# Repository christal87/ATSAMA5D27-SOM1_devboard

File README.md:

# ATSAMA5D27-SOM1_devboard

A custom SAMA5D27 development board I made a while ago for personal experimentation. It's exposing the parallel NAND flash interface to get some hands-on experience using that as a traditional embedded boot device.  

#### TODO:
- [x] PMIC power sequencing works, voltage regulation feedbacks valid, ripple low
- [x] board unique ID readable
- [x] serial console works
- [x] RTC backup supercap works
- [x] default SDMMC0 boots
- [x] USB host VBUS present
- [x] USB High Speed host works
- [x] NAND r/w test OK
- [ ] Configure NAND IOSET and boot config
- [ ] Implement NAND support in the at91bootstrap 2nd level bootloader and U-Boot
- [ ] Compile a kernel and make a rootfs that boots from NAND (buildroot/linux4sam custom board and kernel configs)
- [ ] test (Q)SPI interfaces
- [ ] use (Q)SPI to store the bootloader as NVM
- [ ] test other interfaces (JTAG, UARTs, USB device, ethernet, I^2C, SPI, PIOBU, HSIC)
- [ ] bonus: design and add an eMMC breakout board

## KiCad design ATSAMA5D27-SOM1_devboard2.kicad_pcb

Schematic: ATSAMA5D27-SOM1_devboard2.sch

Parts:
C1, C2, C3, C4, C6, C24, C32: 10uF/25V; C_0805_2012Metric_Pad1.15x1.40mm_HandSolder; Part CL21A106KAYNNNG
C5, C10, C11, C12: 4.7uF/10V; C_0805_2012Metric_Pad1.15x1.40mm_HandSolder; Part CL21A475KPFNNNG
C7: 1F/5.5V; C_Disc_D11.0mm_W5.0mm_P5.00mm
C8, C9, C13, C15, C16, C18, C19, C22, C23, C25, C26, C27, C28, C30, C31, C33, C34, C35, C36, C37, C38, C41, C42, C43: 100nF; C_0805_2012Metric_Pad1.15x1.40mm_HandSolder; Part C0805C104M5RACTU
C14, C17, C20, C21: 2.2uF/16V; C_0805_2012Metric_Pad1.15x1.40mm_HandSolder; Part CL21A225KOFNNNE
C29: 20pF; C_0805_2012Metric_Pad1.15x1.40mm_HandSolder; Part C0805C200J5HACTU
C39, C40: 560pF; C_0805_2012Metric_Pad1.15x1.40mm_HandSolder; Part C0805C561M5RACTU
D1: STPS1L60ZF; D_SOD-123; Part STPS1L60ZF
D2: BAT54C; SOT-23; Part BAT54C
FB1, FB2, FB3, FB4, FB5, FB6, FB7, FB8: 180R; L_0805_2012Metric_Pad1.15x1.40mm_HandSolder; Part BLM21SP181SH1D
IC1: MIC23451-AAAYFL-T5; MIC23451AAAYFLT5; Manufacturer_Part_Number MIC23451-AAAYFL-T5; Mouser Part Number 998-MIC23451-AAAYFL
IC2: TMUX1219DCKR; SOT65P210X110-6N; Manufacturer_Part_Number TMUX1219DCKR; Mouser Part Number 595-TMUX1219DCKR
IC3: ATSAMA5D27-SOM1; ATSAMA5D27SOM1; Manufacturer_Part_Number ATSAMA5D27-SOM1; Mouser Part Number 556-ATSAMA5D27-SOM1
IC4, IC6, IC9: IS25LP512M-JLLE; SON127P800X600X80-9N; Manufacturer_Part_Number IS25LP512M-JLLE; Mouser Part Number 870-IS25LP512M-JLLE
IC5: MT29F32G08CBADBWP-12IT:D; SOP50P2000X120-48N; Manufacturer_Part_Number MT29F32G08ABAAAWP-ITZ:A; Mouser Part Number 340-200226-TRAY
IC7: NL17SZ126DFT2G; SOT65P210X110-5N; Manufacturer_Part_Number NL17SZ126DFT2G; Mouser Part Number 863-NL17SZ126DFT2G
IC8: MIC2025-1YM; SOIC127P602X173-8N; Manufacturer_Part_Number MIC2025-1YM; Mouser Part Number 998-MIC2025-1YM
IC10: ATA6561-GBQW-N; SON65P300X300X90-9N-D; Manufacturer_Part_Number ATA6561-GBQW-N; Mouser Part Number 579-ATA6561-GBQW-N
J2, J3: 22-28-4080; PinHeader_1x08_P2.54mm_Vertical; Part 22-28-4080
J4: 22-28-4020; PinHeader_1x02_P2.54mm_Vertical; Part 22-28-4020
J5: 77313-101-10LF; PinHeader_2x05_P2.54mm_Vertical_SMD; Part 77313-101-10LF
J6: PJ-102AH; BarrelJack_CUI_PJ-102AH_Horizontal; Part PJ-102AH
J7, J8, J9, J10, J11: 22-28-4050; PinHeader_1x05_P2.54mm_Vertical; Part 22-28-4050
J13: 87520-0010BLF; 875200010BLF; Manufacturer_Part_Number 87520-0010BLF; Mouser Part Number 649-87520-0010BLF
J14: 5-2337992-4 (w/o PoE: KRJ45-109NL); 523379924; Manufacturer_Part_Number 5-2337992-4; Mouser Part Number 571-5-2337992-4
J15: 10103594-0001LF; USB_Micro-B_Amphenol_10103594-0001LF_Horizontal; Part 10103594-0001LF
J16: DM1AA-SF-PEJ_21_; DM1AA-SF-PEJ_21__1; Manufacturer_Part_Number DM1AA-SF-PEJ(21); Mouser Part Number 798-DM1AA-SF-PEJ21
J17: 77313-101-16LF; PinHeader_2x08_P2.54mm_Vertical; Part 77313-101-16LF
J18, J20: 77313-101-10LF; PinHeader_2x05_P2.54mm_Vertical; Part 77313-101-10LF
J19: 77313-101-14LF; PinHeader_2x07_P2.54mm_Vertical; Part 77313-101-14LF
J21, J22: 22-28-4030; PinHeader_1x03_P2.54mm_Vertical; Part 22-28-4030
JP1, JP4, JP5, JP6: SolderJumper3; SolderJumper-3_P2.0mm_Open_TrianglePad1.0x1.5mm_NumberLabels; Part 22-28-4030
JP2, JP3, JP7, JP8, JP9, JP10: SolderJumper2; SolderJumper-2_P1.3mm_Open_TrianglePad1.0x1.5mm; Part 22-28-4020
L1, L2, L3: 1uH/2.2A; L_1210_3225Metric_Pad1.42x2.65mm_HandSolder; Part BRL3225T1R0M
Q1, Q2: BSS138; SOT-23
R1, R4, R5, R14, R18, R22, R23, R24, R25, R26, R27, R39, R41, R44, R45, R46, R47, R51, R53, R54, R56: 10k; R_0805_2012Metric_Pad1.15x1.40mm_HandSolder; Part CRCW080510K0FKEAC
R2, R3, R9, R11, R13, R17, R37, R40, R48: 100k; R_0805_2012Metric_Pad1.15x1.40mm_HandSolder; Part CRCW0805100KJNEAC
R6, R7, R8, R10, R20, R21, R34, R35, R36, R38, R60, R61, R63, R64: 0R; R_0805_2012Metric_Pad1.15x1.40mm_HandSolder; Part CRCW08050000Z0EAC
R12, R15, R16, R19, R58, R59: 100R; R_0805_2012Metric_Pad1.15x1.40mm_HandSolder; Part CRCW0805100RFKEAC
R28: 301k; R_0805_2012Metric_Pad1.15x1.40mm_HandSolder; Part CRCW0805301KFKEA
R29: 158k; R_0805_2012Metric_Pad1.15x1.40mm_HandSolder; Part CRCW0805158KFKEA
R30, R32: 309k; R_0805_2012Metric_Pad1.15x1.40mm_HandSolder; Part CRCW0805309KFKEA
R31, R33: 71.5k; R_0805_2012Metric_Pad1.15x1.40mm_HandSolder; Part CRCW080571K5FKEA
R42: 10k (DNP); R_0805_2012Metric_Pad1.15x1.40mm_HandSolder; Part CRCW080510K0FKEAC
R43: 10k; R_0805_2012Metric_Pad1.15x1.40mm_HandSolder; part CRCW080510K0FKEAC
R49, R50: 470R; R_0805_2012Metric_Pad1.15x1.40mm_HandSolder; Part CRCW0805470RFKEAC
R52: 200k; R_0805_2012Metric_Pad1.15x1.40mm_HandSolder; Part CRCW0805200KJNEAC
R55: 22k; R_0805_2012Metric_Pad1.15x1.40mm_HandSolder; Part CRCW080522K0FKEAC
R57: 4k7; R_0805_2012Metric_Pad1.15x1.40mm_HandSolder; Part CRCW08054K70FKEAC
R62: 120R; R_0805_2012Metric_Pad1.15x1.40mm_HandSolder; Part CRCW0805120RFKEAC
RN1, RN2: 68k; R_Cat16-4; Part CAY16-683J4LF
RN3, RN4: 330R; R_Cat16-4; Part CAY16-331J4LF
SW1, SW2, SW3: PTS645SM43SMTR92LFS; SW_SPST_PTS645; Part PTS645SM43SMTR92LFS
U1: NCP1117-3.3_SOT223; SOT-223-3_TabPin2
U2: MCP2551-I-SN; SOIC-8_3.9x4.9mm_P1.27mm

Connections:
BB_PWR_GOOD: IC1.13 (PG3), IC3.28 (PD08/NANDRDY), R14.1
CAN0_RX: C36.1, IC10.4 (RXD), JP6.1 (A)
CAN0_TX: IC10.1 (TXD), JP5.1 (A)
CAN1_RX: IC3.114 (PC27/PCK1/CANRX1/A16), R55.1, R56.1
CAN1_TX: IC3.115 (PC26/CANTX1/A15), U2.1 (TXD)
CLK_AUDIO: IC3.61 (CLK_AUDIO)
COMPN: IC3.64 (COMPN), J19.4
COMPP: IC3.63 (COMPP), J19.2
CS_QSPI1: IC6.1 (CE#), IC7.4 (OUT_Y), R47.2
DISABLE_BOOT: IC3.126 (DIS_BOOT), IC7.1 (OE), JP7.2, R45.2
D_UART1_RXD: IC3.23 (PD02/URXD1/A25), J10.5
D_UART1_TXD: IC3.24 (PD03/UTXD1/FIQ/NWAIT), J10.4
ETH_LED0: IC3.36 (ETH_LED0), J14.P11
ETH_RX+: IC3.38 (ETH_RXP), J14.P3
ETH_RX-: IC3.37 (ETH_RXM), J14.P6
ETH_TX+: IC3.41 (ETH_TXP), J14.P1
ETH_TX-: IC3.40 (ETH_TXM), J14.P2
FLEXCOM0_IO0: IC3.167 (PB28/LCDDAT17/FLEXCOM0_IO0/TIOA5), J3.4
FLEXCOM0_IO1: IC3.144 (PB29/LCDDAT18/FLEXCOM0_IO1/TIOB5), J3.5
FLEXCOM0_IO2: IC3.165 (PB30/LCDDAT19/FLEXCOM0_IO2/TCLK5), J3.6
FLEXCOM0_IO3: IC3.143 (PB31/LCDDAT20/FLEXCOM0_IO3), J3.7
FLEXCOM0_IO4: IC3.145 (PC00/LCDDAT21/FLEXCOM0_IO4), J3.8
FLEXCOM3_IO0: IC3.14 (PC20/ISI_D11/FLEXCOM3_IO0/A9), J2.4
FLEXCOM3_IO1: IC3.6 (PC19/ISI_D10/FLEXCOM3_IO1/A8), J2.5
FLEXCOM3_IO2: IC3.172 (PC18/ISI_D9/FLEXCOM3_IO2/A7), J2.6
FLEXCOM3_IO3: IC3.7 (PC21/ISI_PCK/FLEXCOM3_IO3/A10), J2.7
FLEXCOM3_IO4: IC3.11 (PC22/ISI_VSYNC/FLEXCOM3_IO4/A11), J2.8
FLEXCOM4_IO0: IC3.117 (PC28/FLEXCOM4_IO0/PCK2/A17)
FLEXCOM4_IO1: IC3.118 (PC29/FLEXCOM4_IO1/A18)
FLEXCOM4_IO2: IC3.120 (PC30/FLEXCOM4_IO2/A19)
FLEXCOM4_IO3: IC3.116 (PC31/FLEXCOM4_IO3/URXD3/A20)
FLEXCOM4_IO4: IC3.121 (PD00/FLEXCOM4_IO4/UTXD3/A23)
GND: C1.2, C2.2, C3.2, C4.2, C5.2, C6.2, C7.2, C8.2, C9.2, C10.2, C11.2, C12.2, C13.2, C14.2, C15.1, C16.1, C17.1, C18.1, C19.1, C20.1, C21.1, C22.2, C23.2, C24.2, C25.2, C26.2, C27.2, C28.2, C29.2, C30.2, C31.2, C32.2, C33.2, C34.2, C35.2, C36.2, C37.1, C38.2, C39.2, C40.2, C41.2, C42.2, C43.1, FB5.1, FB6.1, FB8.1, IC1.1 (PGND_1), IC1.2 (PGND_2), IC1.10 (PGND_3), IC1.11 (AGND_1), IC1.24 (AGND_2), IC1.27 (EP1), IC1.28 (EP2), IC2.3 (GND), IC3.1 (GND_00), IC3.10 (GND_01), IC3.18 (GND_02), IC3.26 (GND_03), IC3.31 (GND_04), IC3.39 (GND_05), IC3.42 (GND_06), IC3.43 (GND_07), IC3.50 (GND_08), IC3.56 (GND_09), IC3.62 (GND_10), IC3.66 (GND_11), IC3.69 (GND_12), IC3.72 (GND_13), IC3.75 (GND_14), IC3.88 (GND_15), IC3.89 (GND_16), IC3.98 (GND_17), IC3.107 (GND_18), IC3.130 (GND_19), IC3.131 (GND_20), IC3.149 (GND_21), IC3.166 (GND_22), IC3.171 (GND_23), IC3.176 (GND_24), IC4.4 (GND), IC5.13 (VSS_1), IC5.36 (VSS_2), IC6.4 (GND), IC7.3 (GND), IC8.3 (GND), IC9.4 (GND), IC10.2 (GND), IC10.9 (EP), J2.1, J3.1, J5.3, J5.5, J5.9, J6.2, J7.1, J8.1, J9.1, J10.1, J11.1, J13.4, J14.P10, J15.5 (GND), J16.3, J16.12 (WRITE_PROTECTION_SWITCH_2), J17.14, J17.15, J17.16, J18.10, J19.8, J19.10, J19.12, J19.14, J20.10, J21.2, J22.2, JP7.1, JP8.2, Q1.2 (S), Q2.2 (S), R5.2, R27.2, R29.2, R31.2, R33.2, R42.1, R52.1, R54.2, R55.2, R57.2, R60.1, SW1.2, SW2.2, SW3.2, U1.1 (GND), U2.2 (VSS)
HSIC_DATA: IC3.74 (DATA), J4.2
HSIC_STROBE: IC3.73 (STROBE), J4.1
JTAG_TCK: IC3.53 (PD27/JTAG_TCK), J5.4, R13.1
JTAG_TDI: IC3.51 (PD28/JTAG_TDI), J5.8, R11.1
JTAG_TDO: IC3.52 (PD29/JTAG_TDO), J5.6
JTAG_TMS: IC3.54 (PD30/JTAG_TMS), J5.2, R9.1
NAND_ALE: IC3.119 (PB00/SPI0_MOSI/PWMH1), IC5.17 (ALE)
NAND_CE: IC3.93 (PA31/SPI0_MISO/PWML0/CLASSD_L3), IC5.9 (CE#), R37.1
NAND_CLE: IC3.122 (PB01/SPI0_SPCK/PWML1/CLASSD_R0), IC5.16 (CLE)
NAND_D0: IC3.106 (PA22/FLEXCOM1_IO2/SPI1_SPCK/SDMMC1_CK/Q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), IC5.29 (DQ0)
NAND_D1: IC3.102 (PA23/FLEXCOM1_IO1/SPI1_MOSI/QSPI0_CS), IC5.30 (DQ1)
NAND_D2: IC3.99 (PA24/FLEXCOM1_IO0/SPI1_MISO/QSPI0_IO0), IC5.31 (DQ2)
NAND_D3: IC3.97 (PA25/FLEXCOM1_IO3/SPI1_NPCS0/QSPI0_IO1), IC5.32 (DQ3)
NAND_D4: IC3.100 (PA26/FLEXCOM1_IO4/SPI1_NPCS1/QSPI0_IO2), IC5.41 (DQ4)
NAND_D5: IC3.90 (PA27/TIOA1/SPI0_NPCS2/SPI1_NPCS2/SDMMC1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), IC5.42 (DQ5)
NAND_D6: IC3.95 (PA28/TIOB1/SPI0_NPCS3/SPI1_NPCS3/SDMMC1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), IC5.43 (DQ6)
NAND_D7: IC3.96 (PA29/TCLK1/SPI0_NPCS1/SDMMC1_WP/CLASSD_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), IC5.44 (DQ7)
NAND_RDY: IC3.138 (PC08/LCDDEN/FIQ/PCK0/UTXD1), R35.2
NAND_RE: IC3.124 (PB02/PWMFI0/CLASSD_R1), R36.2
NAND_WE: IC3.94 (PA30/SPI0_NPCS0/PWMH0/SDMMC1_CD/CLASSD_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), R38.2
NRST: IC3.60 (NRST), R10.1, R15.2
unnamed: C1.1, C2.1, C4.1, IC1.5 (PVIN2), IC1.8 (PVIN3), IC1.25 (PVIN1), JP1.2 (C), R8.2, R12.2
unnamed: C5.1, IC1.3 (AVIN1), IC1.6 (AVIN2), IC1.9 (AVIN3), R12.1
unnamed: C7.1, D2.1, R19.1
unnamed: C8.1, D2.3, JP2.1
unnamed: C22.1, J14.P4
unnamed: C23.1, J14.P5
unnamed: C28.1, C32.1, FB7.2, J13.1
unnamed: C39.1, R58.2
unnamed: C40.1, R59.2
unnamed: C41.1, IC10.5 (VIO), R61.2
unnamed: C43.2, R63.2, R64.1
unnamed: D1.1 (K), R19.2
unnamed: FB2.2, JP3.2
unnamed: FB5.2, J13.MH1, J13.MH2
unnamed: FB6.2, J15.6 (Shield)
unnamed: FB7.1, IC8.6 (OUT_1), IC8.8 (OUT_2)
unnamed: FB8.2, J14.MH1, J14.MH2, J14.P8
unnamed: IC1.4 (SW2), L1.1
unnamed: IC1.7 (SW3), L3.1
unnamed: IC1.14 (FB3), R32.2, R33.1
unnamed: IC1.15 (EN3), R20.2, R22.2, R23.2
unnamed: IC1.16 (PG2), R20.1
unnamed: IC1.17 (FB2), R28.2, R29.1
unnamed: IC1.19 (EN2), R21.2, R24.2, R25.2
unnamed: IC1.20 (PG1), R21.1
unnamed: IC1.21 (EN1), R26.2
unnamed: IC1.23 (FB1), R30.2, R31.1
unnamed: IC1.26 (SW1), L2.1
unnamed: IC2.5 (D), R34.2
unnamed: IC3.141 (PC01/LCDDAT22/CANTX0/SPI1_SPCK/I2SCK0), JP5.2 (C)
unnamed: IC3.146 (PC02/LCDDAT23/CANRX0/SPI1_MOSI/I2SMCK0), JP6.2 (C)
unnamed: IC5.7 (R/B#), R35.1, R39.1
unnamed: IC5.8 (RE#), R36.1
unnamed: IC5.18 (WE#), R38.1
unnamed: IC5.19 (WP#), R40.1, R42.2
unnamed: IC5.25 (DNU/VSSQ_1), IC5.48 (DNU/VSSQ_2), JP8.1
unnamed: IC5.34 (DNU/VCCQ_1), IC5.39 (DNU/VCCQ_2), JP9.1
unnamed: IC10.6 (CANL), J22.1, R64.2
unnamed: IC10.7 (CANH), J22.3, R63.1
unnamed: IC10.8 (STBY), R60.2
unnamed: J5.7, R6.1
unnamed: J5.10, R10.2
unnamed: J14.P9, R49.2
unnamed: J14.P12, R50.2
unnamed: J19.1, RN3.8 (R1.2)
unnamed: J19.3, RN3.7 (R2.2)
unnamed: J19.5, RN3.6 (R3.2)
unnamed: J19.7, RN3.5 (R4.2)
unnamed: J19.9, RN4.8 (R1.2)
unnamed: J19.11, RN4.7 (R2.2)
unnamed: J19.13, RN4.6 (R3.2)
unnamed: J21.1, R58.1, R62.2, U2.6 (CANL)
unnamed: J21.3, R59.1, R62.1, U2.7 (CANH)
unnamed: Q1.1 (G), R1.1, R2.1
unnamed: Q1.3 (D), Q2.1 (G), R3.1, SW1.1
unnamed: Q2.3 (D), R4.2, R7.2
unnamed: R5.1, R6.2
unnamed: R15.1, R17.1, SW2.1
unnamed: R16.1, R18.1, SW3.1
unnamed: R7.1, R8.1, R22.1, R24.1, R26.1
unnamed: R56.2, U2.4 (RXD)
unnamed: R57.1, U2.8 (Rs)
PA21: IC3.103 (PA21/PCK2/IRQ/TCLK0/SDMMC1_DAT3/NANDRDY)
PB11: IC3.148 (PB11/LCDDAT0/URXD3/PDMDAT0)
PB12: IC3.151 (PB12/LCDDAT1/UTXD3/PDMCLK0)
PB13: IC3.155 (PB13/LCDDAT2/PCK1)
PB14: IC3.150 (PB14/LCDDAT3/TK1/I2SMCK1)
PB15: IC3.162 (PB15/LCDDAT4/TF1/I2SCK1)
PB16: IC3.154 (PB16/LCDDAT5/TD1/I2SWS1)
PB17: IC3.157 (PB17/LCDDAT6/RD1/I2SDI1)
PB18: IC3.152 (PB18/LCDDAT7/RK1/I2SDO1)
PB19: IC3.158 (PB19/LCDDAT8/RF1/TIOA3)
PB20: IC3.156 (PB20/LCDDAT9/TK0/TIOB3/PCK1)
PB21: IC3.164 (PB21/LCDDAT10/TF0/TCLK3/FLEXCOM3_IO2)
PB22: IC3.161 (PB22/LCDDAT11/TD0/TIOA2/FLEXCOM3_IO1)
PB23: IC3.160 (PB23/LCDDAT12/RD0/TIOB2/FLEXCOM3_IO0)
PB24: IC3.168 (PB24/LCDDAT13/RK0/TCLK2/FLEXCOM3_IO3)
PB25: IC3.159 (PB25/LCDDAT14/RF0/FLEXCOM3_IO4)
PC9: IC3.2 (PC09/FIQ/ISI_D0/TIOA4)
PC10: IC3.9 (PC10/ISI_D1/TIOB4/CANTX0)
PC11: IC3.175 (PC11/ISI_D2/TCLK4/CANRX0/A0/NBS0)
PC14: IC3.8 (PC14/ISI_D5/TD0/A3)
PC15: IC3.12 (PC15/ISI_D6/RD0/A4)
PC16: IC3.174 (PC16/ISI_D7/RK0/A5)
PC17: IC3.5 (PC17/ISI_D8/RF0/A6)
PC23: IC3.170 (PC23/ISI_HSYNC/A12)
PC24: IC3.13 (PC24/ISI_MCK/A13)
PC25: IC3.173 (PC25/ISI_FIELD/A14)
PD1: IC3.113 (PD01/A24)
PD6: IC3.22 (PD06/PCK1/NCS2)
PD7: IC3.25 (PD07/NWR1/NBS1)
PD22: IC3.20 (PD22/EEPROM_TWCK_PD22)
PD23: IC3.30 (PD23/URXD2/AD4)
PD24: IC3.29 (PD24/UTXD2/AD5)
PD25: IC3.110 (PD25/AD6)
PD26: IC3.34 (PD26/AD7)
PIOBU1: IC3.33 (PIOBU1), RN3.1 (R1.1)
PIOBU2: IC3.44 (PIOBU2), RN3.2 (R2.1)
PIOBU3: IC3.48 (PIOBU3), RN3.3 (R3.1)
PIOBU4: IC3.47 (PIOBU4), RN3.4 (R4.1)
PIOBU5: IC3.46 (PIOBU5), RN4.1 (R1.1)
PIOBU6: IC3.59 (PIOBU6), RN4.2 (R2.1)
PIOBU7: IC3.45 (PIOBU7), RN4.3 (R3.1)
QSPI1_CS: IC3.127 (PB06/TIOA2/PWML2/QSPI1_CS), IC7.2 (IN_A)
QSPI1_IO0: IC3.133 (PB07/TIOB2/PWMH3/QSPI1_IO0), IC6.5 (SI_(IO0))
QSPI1_IO1: IC3.128 (PB08/TCLK3/PWML3/QSPI1_IO1), IC6.2 (SO_(IO1))
QSPI1_IO2: IC3.132 (PB09/TIOA3/PWMFI1/QSPI1_IO2), IC6.3 (WP#_(IO2)), R43.2
QSPI1_IO3: IC3.135 (PB10/TIOB3/PWMEXTRG1/QSPI1_IO3), IC6.7 (HOLD#_OR_RESET#_(IO3)), R51.2
QSPI1_SCK: IC3.134 (PB05/TCLK2/PWMH2/QSPI1_SCK), IC6.6 (SCK)
RXD: IC3.32 (RXD), J19.6
SDMMC0_CD: IC3.91 (PA13/SDMMC0_CD/FLEXCOM3_IO1/D8), J16.6, R46.2
SDMMC0_CK: IC3.80 (PA00/SDMMC0_CK/QSPIO0_SLK/D0), J16.5, J17.1
SDMMC0_CMD: IC3.76 (PA01/SDMMC0_CMD/QSPI0_CS/D1), J16.2, J17.3, R41.2
SDMMC0_D0: IC3.83 (PA02/SDMMC0_DAT0/QSPI0_IO0/D2), J16.7, J17.11, RN1.1 (R1.1)
SDMMC0_D1: IC3.81 (PA03/SDMMC0_DAT1/QSPI0_IO1/D3), J16.8, J17.9, RN1.2 (R2.1)
SDMMC0_D2: IC3.84 (PA04/SDMMC0_DAT2/QSPI0_IO2/D4), J16.9, J17.5, RN1.4 (R4.1)
SDMMC0_D3: IC3.85 (PA05/SDMMC0_DAT3/QSPI0_IO3/D5), J16.1, J17.7, RN1.3 (R3.1)
SDMMC0_D4: IC3.86 (PA06/SDMMC0_DAT4/TIOA5/FLEXCOM2_IO0/D6), J17.2, RN2.1 (R1.1)
SDMMC0_D5: IC3.79 (PA07/SDMMC0_DAT5/TIOB5/FLEXCOM2_IO1/D7), J17.4, RN2.2 (R2.1)
SDMMC0_D6: IC3.78 (PA08/SDMMC0_DAT6/TCLK5/FLEXCOM2_IO2/NWE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), J17.6, RN2.3 (R3.1)
SDMMC0_D7: IC3.77 (PA09/SDMMC0_DAT7/TIOA4/FLEXCOM2_IO3/NCS3), J17.8, RN2.4 (R4.1)
SDMMC0_RSTN: IC3.82 (PA10/SDMMC0_RSTN/TIOB4/FLEXCOM2_IO4/A21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), J17.13
SDMMC0_VDDSEL: IC2.1 (SEL), IC3.87 (PA11/SDMMC0_VDDSEL/TCLK4/A22/NANDCLE), R27.1
SDMMC0_WP: IC3.92 (PA12/SDMMC0_WP/IRQ/NRD/NANDOE), J16.11 (WRITE_PROTECTION_SWITCH_1), R44.2
SHDN: IC3.35 (SHDN), R1.2
SPI0_MISO: IC3.112 (PA16/SPI0_MISO/TD1/QSPI0_IO0/I2SWS1/FLE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), IC9.2 (SO_(IO1)), J20.6
SPI0_MOSI: IC3.109 (PA15/SPI0_MOSI/TF1/QSPI0_CS/I2SCK1/FLEX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), IC9.5 (SI_(IO0)), J20.4
SPI0_NPCS0: IC3.108 (PA17/SPI0_NPCS0/RD1/QSPI0_IO1/I2SDI1/FL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), IC9.1 (CE#), J20.8
SPI0_NPCS1: IC3.105 (PA18/SPI0_NPCS1/RK1/QSPI0_IO2/I2SDO1/SD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), J20.1
SPI0_NPCS2: IC3.101 (PA19/SPI0_NPCS2/RF1/QSPI0_IO3/TIOA0/SDM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), J20.2
SPI0_NPCS3: IC3.104 (PA20/SPI0_NPCS3/TIOB0/SDMMC1_DAT2/D15), J20.3
SPI0_SCK: IC3.111 (PA14/SPI0_SPCK/TK1/QSPI0_SCK/I2SMCK1/FL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), IC9.6 (SCK), J20.5
SPI1_MISO: IC3.142 (PC03/LCDPWM/TIOA1/SPI1_MISO/I2SWS0), IC4.2 (SO_(IO1)), J18.6
SPI1_MOSI: IC4.5 (SI_(IO0)), J18.4, JP6.3 (B)
SPI1_NPCS0: IC3.136 (PC04/LCDDISP/TIOB1/SPI1_NPCS0/I2SDI0), IC4.1 (CE#), J18.8
SPI1_NPCS1: IC3.137 (PC05/LCDVSYNC/TCLK1/SPI1_NPCS1/I2SDO0), J18.1
SPI1_NPCS2: IC3.140 (PC06/LCDHSYNC/TWD1/SPI1_NPCS2), J18.2
SPI1_NPCS3: IC3.139 (PC07/LCDPCK/TWCK1/SPI1_NPCS3/URXD1), J18.3
SPI1_SCK: IC4.6 (SCK), J18.5, JP5.3 (B)
TWCK1: IC3.21 (PD05/TWCK1/NCS1), J7.4
TWD1: IC3.27 (PD04/TWD1/NCS0), J7.5
UART0_RXD: IC3.169 (PB26/LCDDAT15/URXD0), J9.5
UART0_TXD: IC3.163 (PB27/LCDDAT16/UTXD0), J9.4
UART3_RXD: IC3.3 (PC12/ISI_D3/URXD3/TK0/A1), J8.5
UART3_TXD: IC3.4 (PC13/ISI_D4/UTXD3/TF0/A2), J8.4
UART4_RXD: IC3.123 (PB03/URXD4/IRQ/PWMEXTRG0/CLASSD_R2), J11.5
UART4_TXD: IC3.125 (PB04/UTXD4/FIQ/CLASSD_R3), J11.4
USBA_D+: IC3.68 (USBA_P), J15.3 (D+)
USBA_D-: IC3.67 (USBA_M), J15.2 (D-)
USBA_VBUS_5V: C33.1, IC3.57 (PD20/TIOA2/TWCK1/AD1), R48.1, R52.2
USBB_D+: IC3.71 (USBB_P), J13.3
USBB_D-: IC3.70 (USBB_M), J13.2
USBB_OVCUR: IC3.58 (PD19/PCK0/TWD1/AD0), IC8.2 (FLG), R53.2
USBB_POWR_EN: IC3.19 (PD21/EEPROM_TWD_PD21), IC8.1 (EN), JP10.2, R54.1
VBUS_USBA: C29.1, J15.1 (VBUS), JP1.1 (A), R48.2
VDDBU: C19.2, C21.2, IC3.55 (VDDBU), JP2.2, R2.2, R17.2, R18.2
VDDIN_3V3: C13.1, C14.1, C15.2, C16.2, C17.2, FB2.1, IC3.15 (VDDISC), IC3.16 (VDDIN_3V3_1), IC3.17 (VDDIN_3V3_2)
VDDSDHC: C18.2, C20.2, IC3.65 (VDDSDHC), JP4.2 (C), R34.1, R41.1, RN1.5 (R4.2), RN1.6 (R3.2), RN1.7 (R2.2), RN1.8 (R1.2), RN2.5 (R4.2), RN2.6 (R3.2), RN2.7 (R2.2), RN2.8 (R1.2)
VDD_3V3: C9.1, C24.1, C25.1, C26.1, C27.1, C30.1, C31.1, C34.1, C42.1, D1.2 (A), D2.2, FB4.1, IC2.2 (VDD), IC4.3 (WP#_(IO2)), IC4.7 (HOLD#_OR_RESET#_(IO3)), IC4.8 (VCC), IC5.12 (VCC_1), IC5.37 (VCC_2), IC6.8 (VCC), IC7.5 (VCC), IC9.3 (WP#_(IO2)), IC9.7 (HOLD#_OR_RESET#_(IO3)), IC9.8 (VCC), J5.1, J16.4, J17.10, J17.12, J18.9, J20.9, JP9.2, R9.2, R11.2, R13.2, R37.2, R39.2, R40.2, R43.1, R44.1, R45.1, R46.1, R47.1, R49.1, R50.1, R51.1, R53.1, R61.1
VDD_SDHC_1V8: FB1.1, IC2.6 (S2), JP4.1 (A)
VDD_SDHC_3V3: FB3.1, IC2.4 (S1), JP4.3 (B)
VEXT_3V3: C6.1, J2.3, J3.3, J7.3, J8.3, J9.3, J10.3, J11.3, U1.2 (VO)
VIN_5V: C3.1, C35.1, C37.2, C38.1, IC8.7 (IN), IC10.3 (VCC), J2.2, J3.2, J6.1, J7.2, J8.2, J9.2, J10.2, J11.2, J18.7, J20.7, JP1.3 (B), JP10.1, R3.2, R4.1, U1.3 (VI), U2.3 (VDD)
VOUT1: C11.1, FB3.2, IC1.22 (SNS1), JP3.1, L2.2, R25.1, R30.1
VOUT2: C10.1, FB1.2, IC1.18 (SNS2), L1.2, R23.1, R28.1
VOUT3: C12.1, FB4.2, IC1.12 (SNS3), L3.2, R14.2, R32.1
WKUP: IC3.49 (WKUP), R16.2

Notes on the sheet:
Fast Ethernet
ONFI Compliance
Top layer power
separate PWR layer fill
Top/bottom layer power
* QSPI1 is only available on IOSET2
* FLEXCOM3_IO0-4 only available on IOSET2
* TWI1 is only available on IOSET2

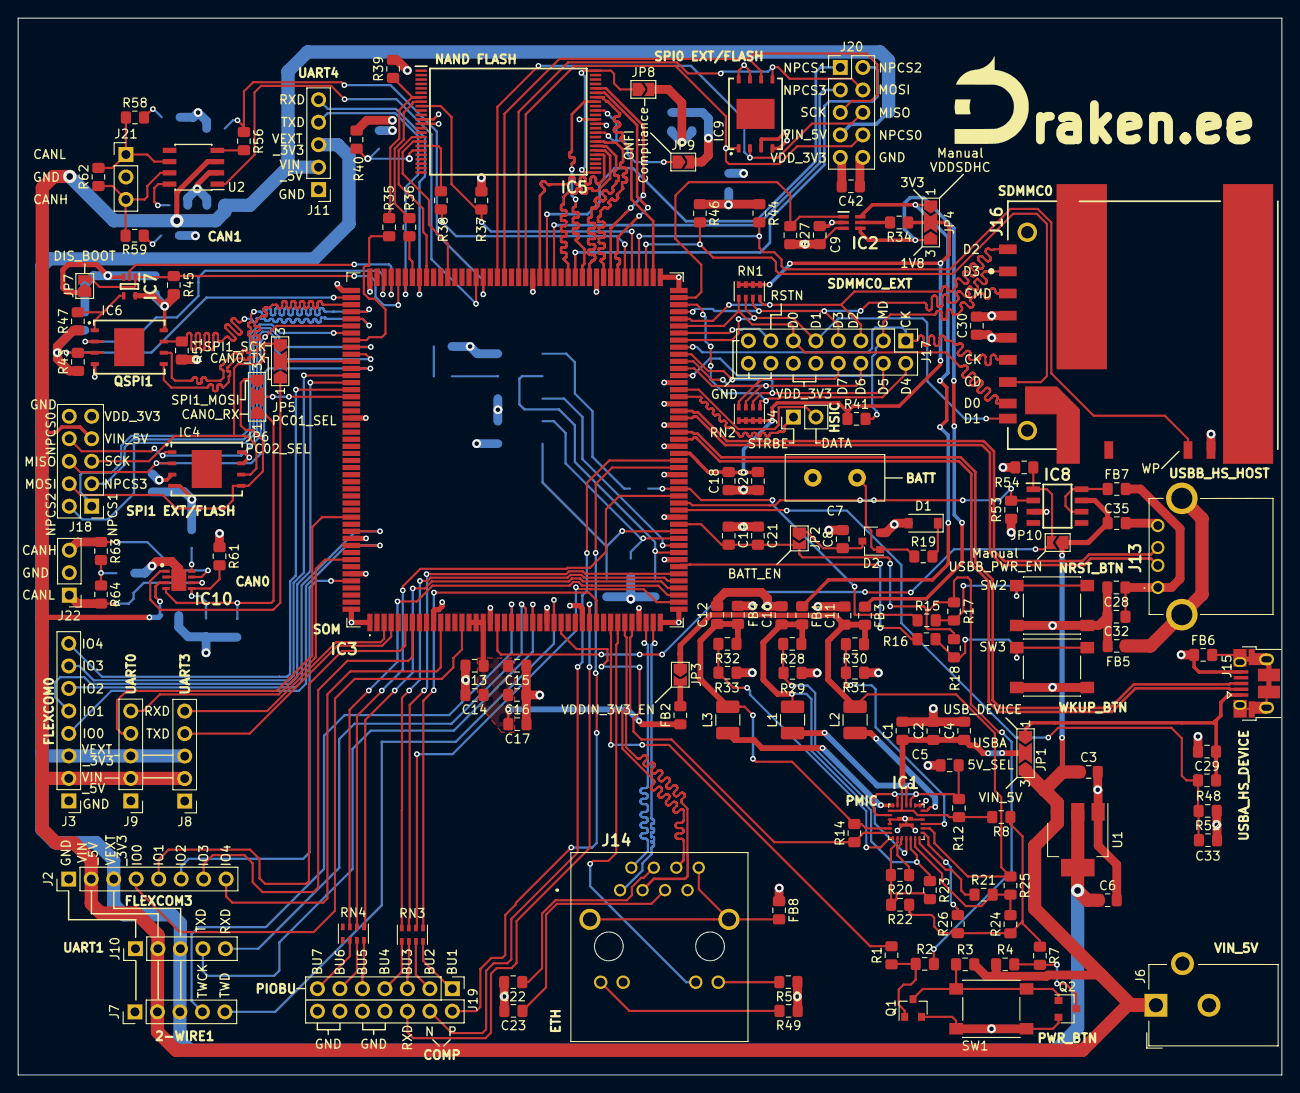
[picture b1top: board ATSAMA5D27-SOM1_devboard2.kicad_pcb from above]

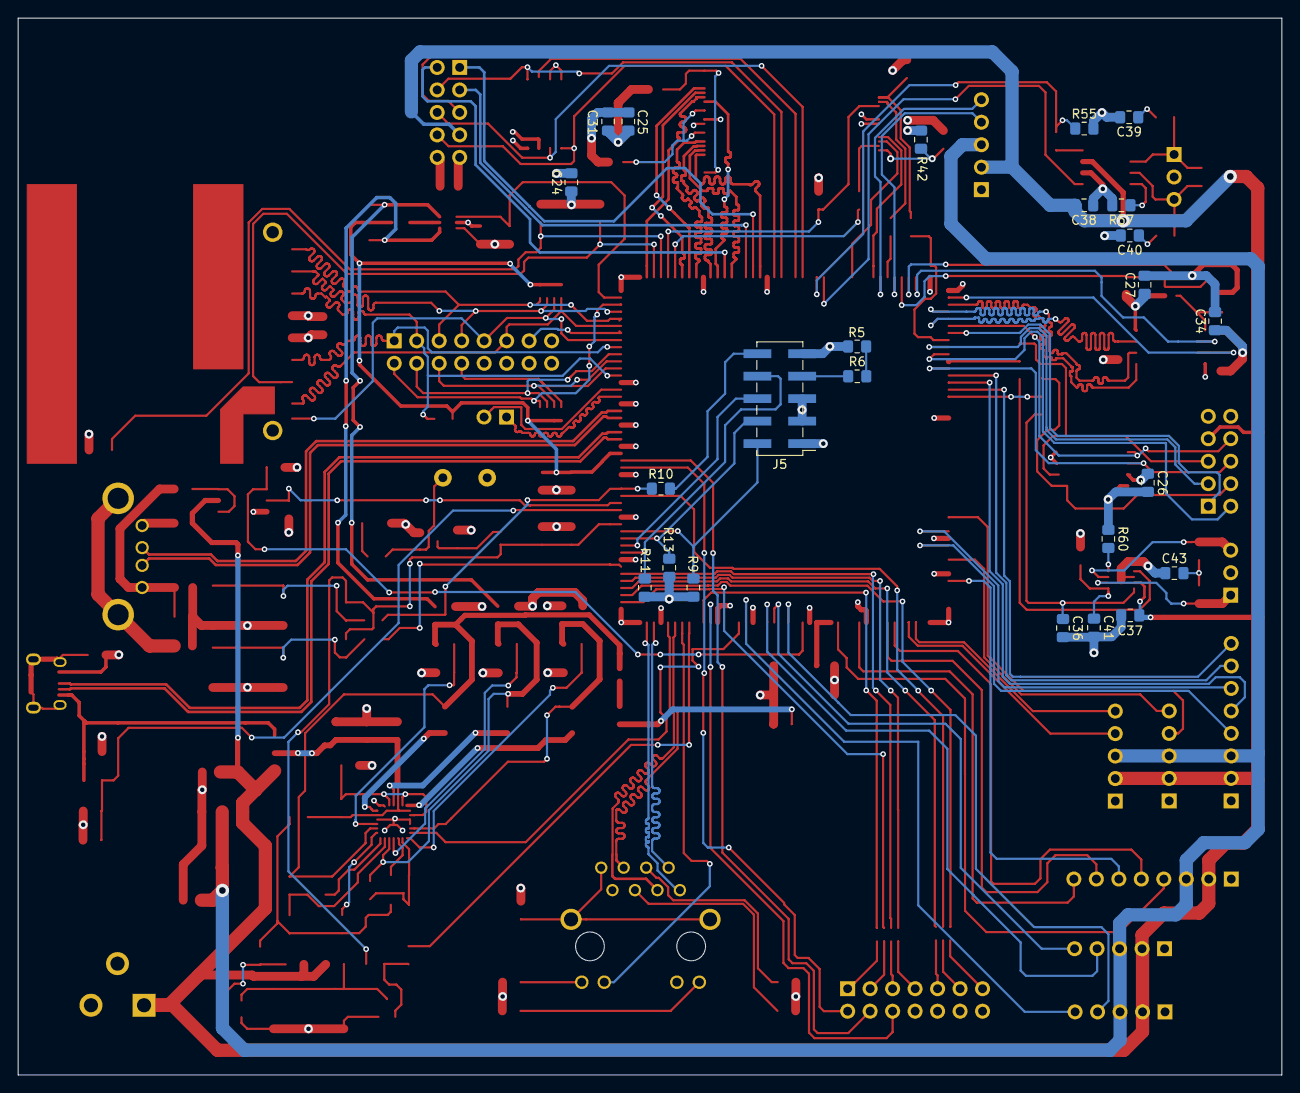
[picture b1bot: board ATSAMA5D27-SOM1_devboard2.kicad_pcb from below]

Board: 4 copper layers, 142.7 x 119.4 mm, 171 parts (24 on the bottom side), 181 nets.

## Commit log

2026-06-09 fix typo
2026-06-09 add photo
